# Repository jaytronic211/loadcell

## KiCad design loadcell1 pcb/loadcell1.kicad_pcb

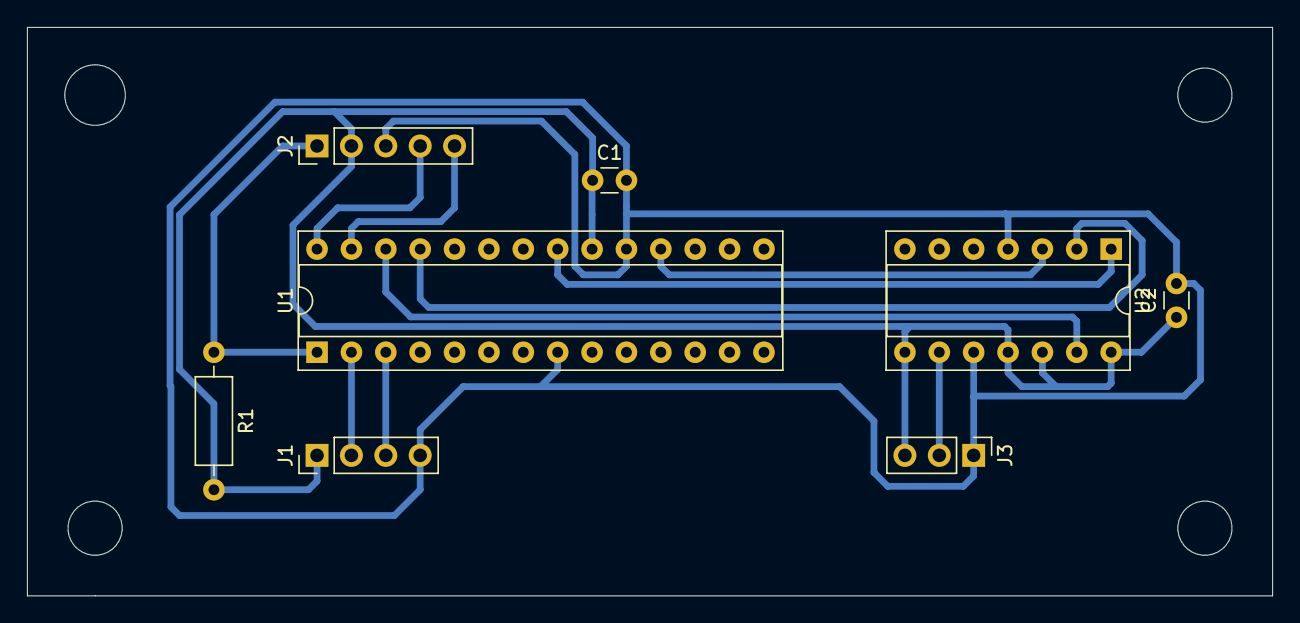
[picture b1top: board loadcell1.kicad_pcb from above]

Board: 2 copper layers, 92.0 x 42.0 mm, 8 parts (0 on the bottom side), 12 nets.

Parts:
C1, C2: C; C_Disc_D3.0mm_W1.6mm_P2.50mm
J1: HX711; PinHeader_1x04_P2.54mm_Vertical
J2: ICSP; PinHeader_1x05_P2.54mm_Vertical
J3: Output; PinHeader_1x03_P2.54mm_Vertical
R1: R; R_Axial_DIN0207_L6.3mm_D2.5mm_P10.16mm_Horizontal
U1: PIC18F27J53_ISS; DIP-28_W7.62mm_Socket
U2: MCP4251-xxxx-P; DIP-14_W7.62mm_Socket

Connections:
+3V3: C1.1, C2.1, J1.1, J2.2, J3.3, R1.2, U1.20, U2.8, U2.11, U2.12, U2.14
GND: C1.2, C2.2, J1.4, J2.3, J3.1, U1.8, U1.19, U2.4, U2.10
unnamed: J1.2, U1.2
unnamed: J1.3, U1.3
unnamed: J2.1, R1.1, U1.1
unnamed: J2.4, U1.28
unnamed: J2.5, U1.27
unnamed: J3.2, U2.9
unnamed: U1.18, U2.3
unnamed: U1.21, U2.1
unnamed: U1.25, U2.2
unnamed: U1.26, U2.13
